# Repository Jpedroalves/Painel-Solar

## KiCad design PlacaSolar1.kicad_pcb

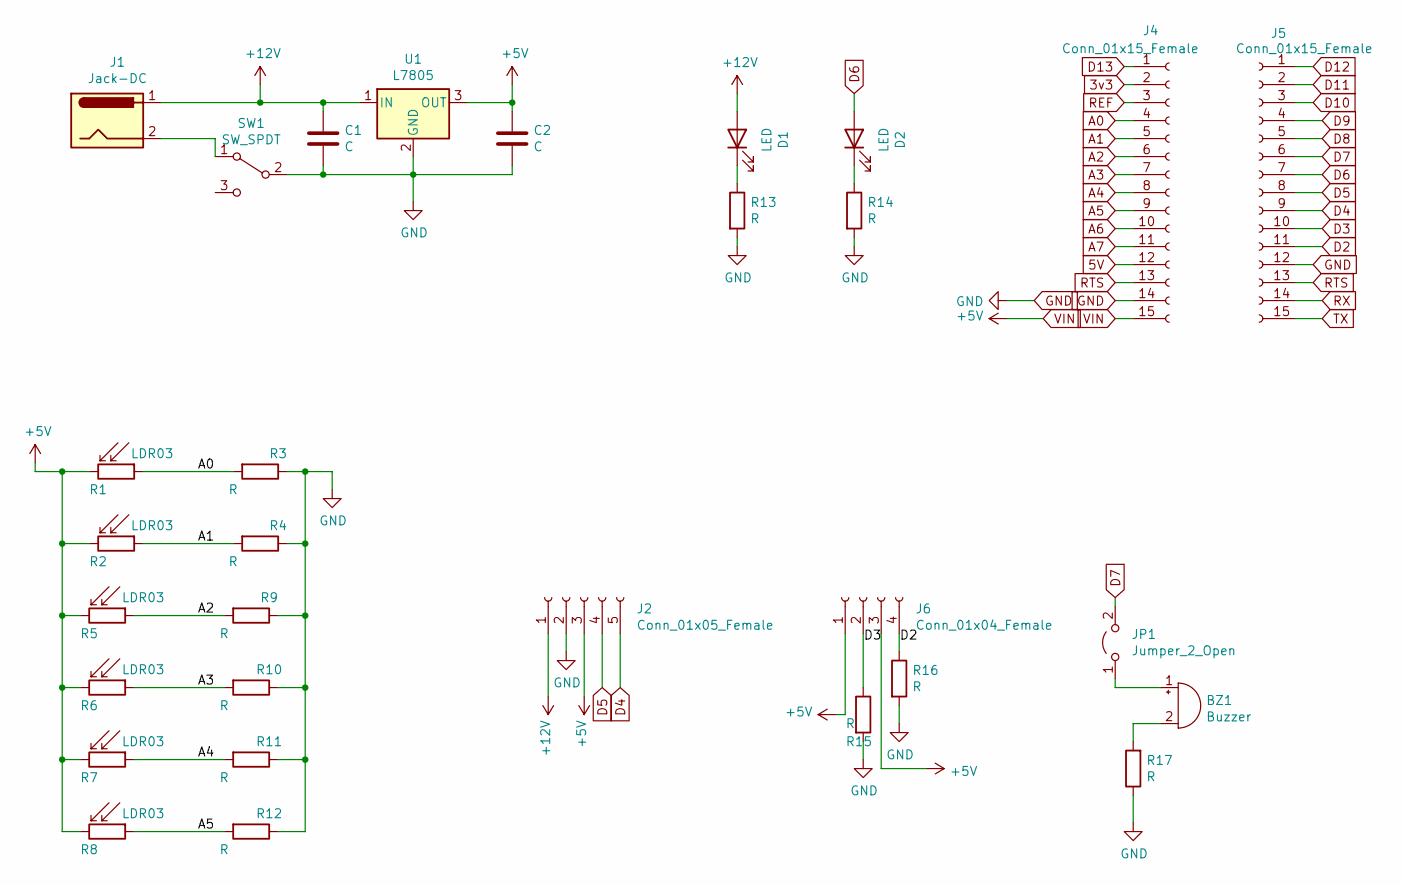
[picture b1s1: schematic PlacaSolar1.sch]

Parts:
BZ1: Buzzer; Buzzer_12x9.5RM7.6
C1, C2: C; CP_Radial_D5.0mm_P2.50mm
D1, D2: LED; LED_D5.0mm
J1: Jack-DC; BarrelJack_Horizontal
J2: Conn_01x05_Female; PinHeader_1x05_P2.54mm_Vertical
J4, J5: Conn_01x15_Female; PinSocket_1x15_P2.54mm_Vertical
J6: Conn_01x04_Female; Borne_LAB_4
JP1: Jumper_2_Open; PinHeader_1x02_P2.54mm_Vertical
R1, R2, R5, R6, R7, R8: LDR03; Borne_LAB_2
R3, R4, R9, R10, R11, R12, R13, R14, R15, R16, R17: R; R_Axial_DIN0207_L6.3mm_D2.5mm_P10.16mm_Horizontal
SW1: SW_SPDT; TE_2267077-2
U1: L7805; TO-220-3_Vertical

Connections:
3v3: J4.2
5V: J4.12
+12V: C1.1, D1.2 (A), J1.1, J2.1, U1.1 (IN)
A0: J4.4, R1.1, R3.2
A1: J4.5, R2.1, R4.2
A2: J4.6, R5.1, R9.2
A3: J4.7, R6.1, R10.2
A4: J4.8, R7.1, R11.2
A5: J4.9, R8.1, R12.2
A6: J4.10
A7: J4.11
D2: J5.11, J6.4, R16.1
D3: J5.10, J6.2, R15.1
D4: J2.5, J5.9
D5: J2.4, J5.8
D6: D2.2 (A), J5.7
D7: J5.6, JP1.2 (B)
D8: J5.5
D9: J5.4
D10: J5.3
D11: J5.2
D12: J5.1
D13: J4.1
GND: C1.2, C2.2, J2.2, J4.14, J5.12, R3.1, R4.1, R9.1, R10.1, R11.1, R12.1, R13.2, R14.2, R15.2, R16.2, R17.1, SW1.2 (B), U1.2 (GND)
unnamed: BZ1.1 (-), JP1.1 (A)
unnamed: BZ1.2 (+), R17.2
unnamed: D1.1 (K), R13.1
unnamed: D2.1 (K), R14.1
unnamed: J1.2, SW1.1 (A)
REF: J4.3
RTS: J4.13, J5.13
RX: J5.14
TX: J5.15
VIN: C2.1, J2.3, J4.15, J6.1, J6.3, R1.2, R2.2, R5.2, R6.2, R7.2, R8.2, U1.3 (OUT)

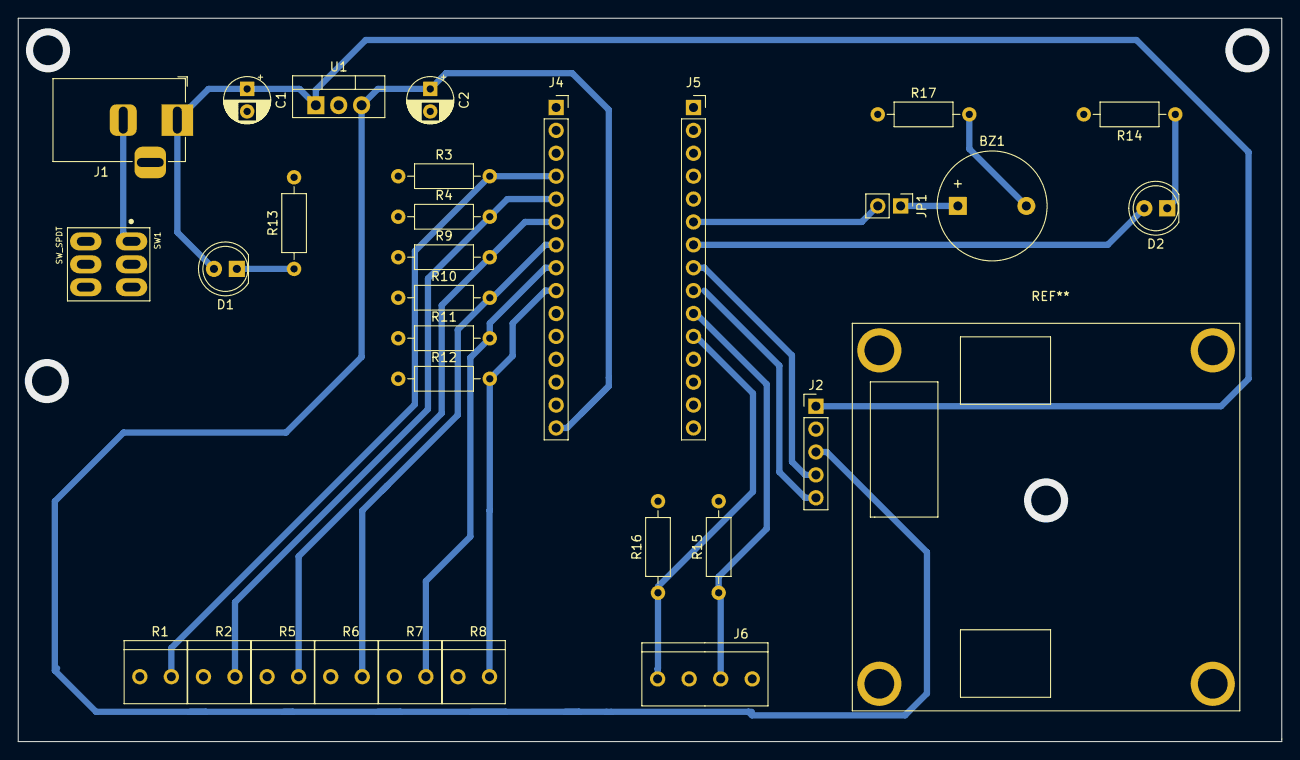
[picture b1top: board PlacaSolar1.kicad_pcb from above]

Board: 2 copper layers, 140.2 x 80.3 mm, 30 parts (0 on the bottom side), 21 nets.

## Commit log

2021-09-09 Primeira versao
2021-09-09 Atualizando esquemático
2021-09-10 Adicionando a footprint dos componentes
2021-09-10 Adicionando botão de reset ao esquemático
2021-09-11 Corrigindo footprint dos LDRs
2021-09-11 Corrigindo footprint do interruptor e adicionando alguns modelos 3d
2021-09-11 Adicionando modelos 3d, falta o modelo dos bornes, inicio da PCB
2021-09-12 Removendo botão de Reset
2021-09-13 Primeira versão de trilhas da PCB, falta verificar o tamanho de certos componentes
2021-09-14 Corrigindo disposição dos componentes e das trilhas para caber na pcb de 14x8cm
2021-09-14 Corrigindo tamanho dos bornes 7x7cm
